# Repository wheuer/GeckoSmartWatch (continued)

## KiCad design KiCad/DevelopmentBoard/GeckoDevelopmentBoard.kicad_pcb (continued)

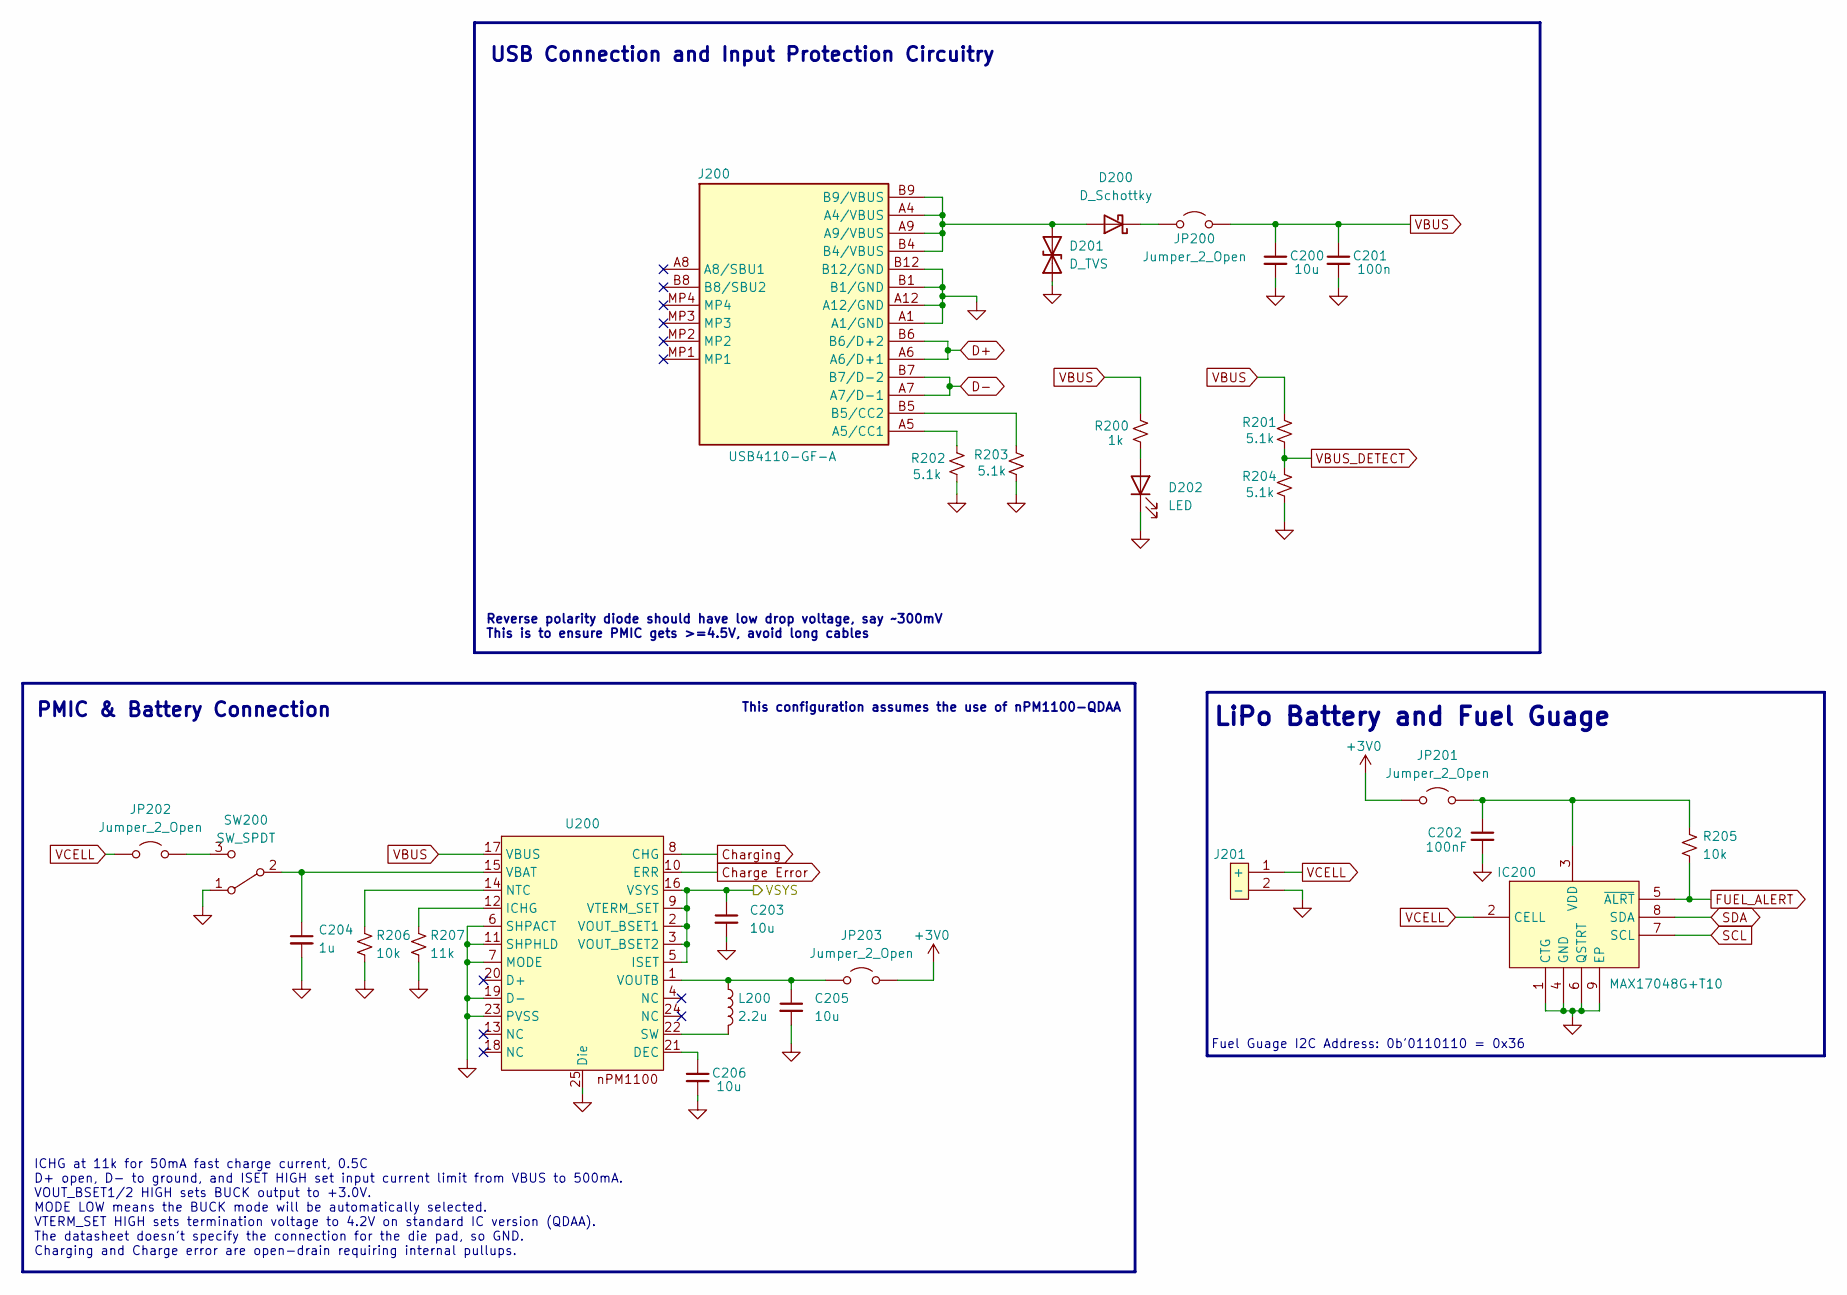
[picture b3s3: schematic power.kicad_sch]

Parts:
C200, C203, C205, C206: 10u; C_0402_1005Metric
C201: 100n; C_0402_1005Metric
C202: 100nF; C_0402_1005Metric
C204: 1u; C_0402_1005Metric
D200: D_Schottky; reversePolarity_SODFL3616X98N
D201: D_TVS; TVS_SOD2513X120N
D202: LED; LED_0603_1608Metric
IC200: MAX17048G+T10; MAX17048_fuelGuague; Mouser Part Number 700-MAX17048G+T10
J200: USB4110-GF-A; USB4110GFA; Mouser Part Number 640-USB4110-GF-A
J201: 1769_LiPoConnector; 1769_lipoConnector; Mouser Part Number 485-1769
JP200, JP201, JP202, JP203: Jumper_2_Open; 2pinJumper_HDRV2W110P0X254_1X2_508X254X854P
L200: 2.2u; L_0402_1005Metric
R200: 1k; R_0402_1005Metric
R201, R202, R203, R204: 5.1k; R_0402_1005Metric
R205, R206: 10k; R_0402_1005Metric
R207: 11k; R_0402_1005Metric
SW200: SW_SPDT; largerSlide_SW_JS102011JAQN
U200: nPM1100_QFN50P400X400X90-25N-D

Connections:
+3V0: JP201.1 (A), JP203.1 (A); also elsewhere on the board
/Power/VSYS: C203.1, U200.2 (VOUT_BSET1), U200.3 (VOUT_BSET2), U200.5 (ISET), U200.9 (VTERM_SET), U200.16 (VSYS)
Charge Error: U200.10 (ERR); also elsewhere on the board
Charging: U200.8 (CHG); also elsewhere on the board
D+: J200.A6 (A6/D+1), J200.B6 (B6/D+2); also elsewhere on the board
D-: J200.A7 (A7/D-1), J200.B7 (B7/D-2); also elsewhere on the board
FUEL_ALERT: IC200.5 (~ALRT), R205.1; also elsewhere on the board
GND: C200.2, C201.2, C202.2, C203.2, C204.2, C205.2, C206.2, D201.1 (A1), D202.1 (K), IC200.1 (CTG), IC200.4 (GND), IC200.6 (QSTRT), IC200.9 (EP), J200.A1 (A1/GND), J200.A12 (A12/GND), J200.B1 (B1/GND), J200.B12 (B12/GND), J201.2 (-), R202.1, R203.1, R204.1, R206.2, R207.2, SW200.1 (A), U200.6 (SHPACT), U200.7 (MODE), U200.11 (SHPHLD), U200.19 (D-), U200.23 (PVSS), U200.25 (Die); also elsewhere on the board
unnamed: D200.2 (A), D201.2 (A2), J200.A4 (A4/VBUS), J200.A9 (A9/VBUS), J200.B4 (B4/VBUS), J200.B9 (B9/VBUS)
unnamed: D200.1 (K), JP200.2 (B)
unnamed: D202.2 (A), R200.2
unnamed: C202.1, IC200.3 (VDD), JP201.2 (B), R205.2
unnamed: J200.A5 (A5/CC1), R202.2
unnamed: J200.B5 (B5/CC2), R203.2
unnamed: JP202.2 (B), SW200.3 (C)
unnamed: C205.1, JP203.2 (B), L200.1, U200.1 (VOUTB)
unnamed: C204.1, SW200.2 (B), U200.15 (VBAT)
unnamed: C206.1, U200.21 (DEC)
unnamed: R207.1, U200.12 (ICHG)
unnamed: R206.1, U200.14 (NTC)
unnamed: L200.2, U200.22 (SW)
SCL: IC200.7 (SCL); also elsewhere on the board
SDA: IC200.8 (SDA); also elsewhere on the board
VBUS: C200.1, C201.1, JP200.1 (A), R200.1, R201.2, U200.17 (VBUS); also elsewhere on the board
VBUS_DETECT: R201.1, R204.2; also elsewhere on the board
VCELL: IC200.2 (CELL), J201.1 (+), JP202.1 (A)

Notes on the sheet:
This configuration assumes the use of nPM1100-QDAA
USB Connection and Input Protection Circuitry
ICHG at 11k for 50mA fast charge current, 0.5C D+ open, D- to ground, and ISET HIGH set input current limit from VBUS to 500mA. VOUT_BSET1/2 HIGH sets BUCK output to +3.0V. MODE LOW means the BUCK mode will be automatically selected. VTERM_SET HIGH sets termination voltage to 4.2V on standard IC ve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
Fuel Guage I2C Address: 0b'0110110 = 0x36
PMIC & Battery Connection
Reverse polarity diode should have low drop voltage, say ~300mV This is to ensure PMIC gets >=4.5V, avoid long cables
LiPo Battery and Fuel Guage

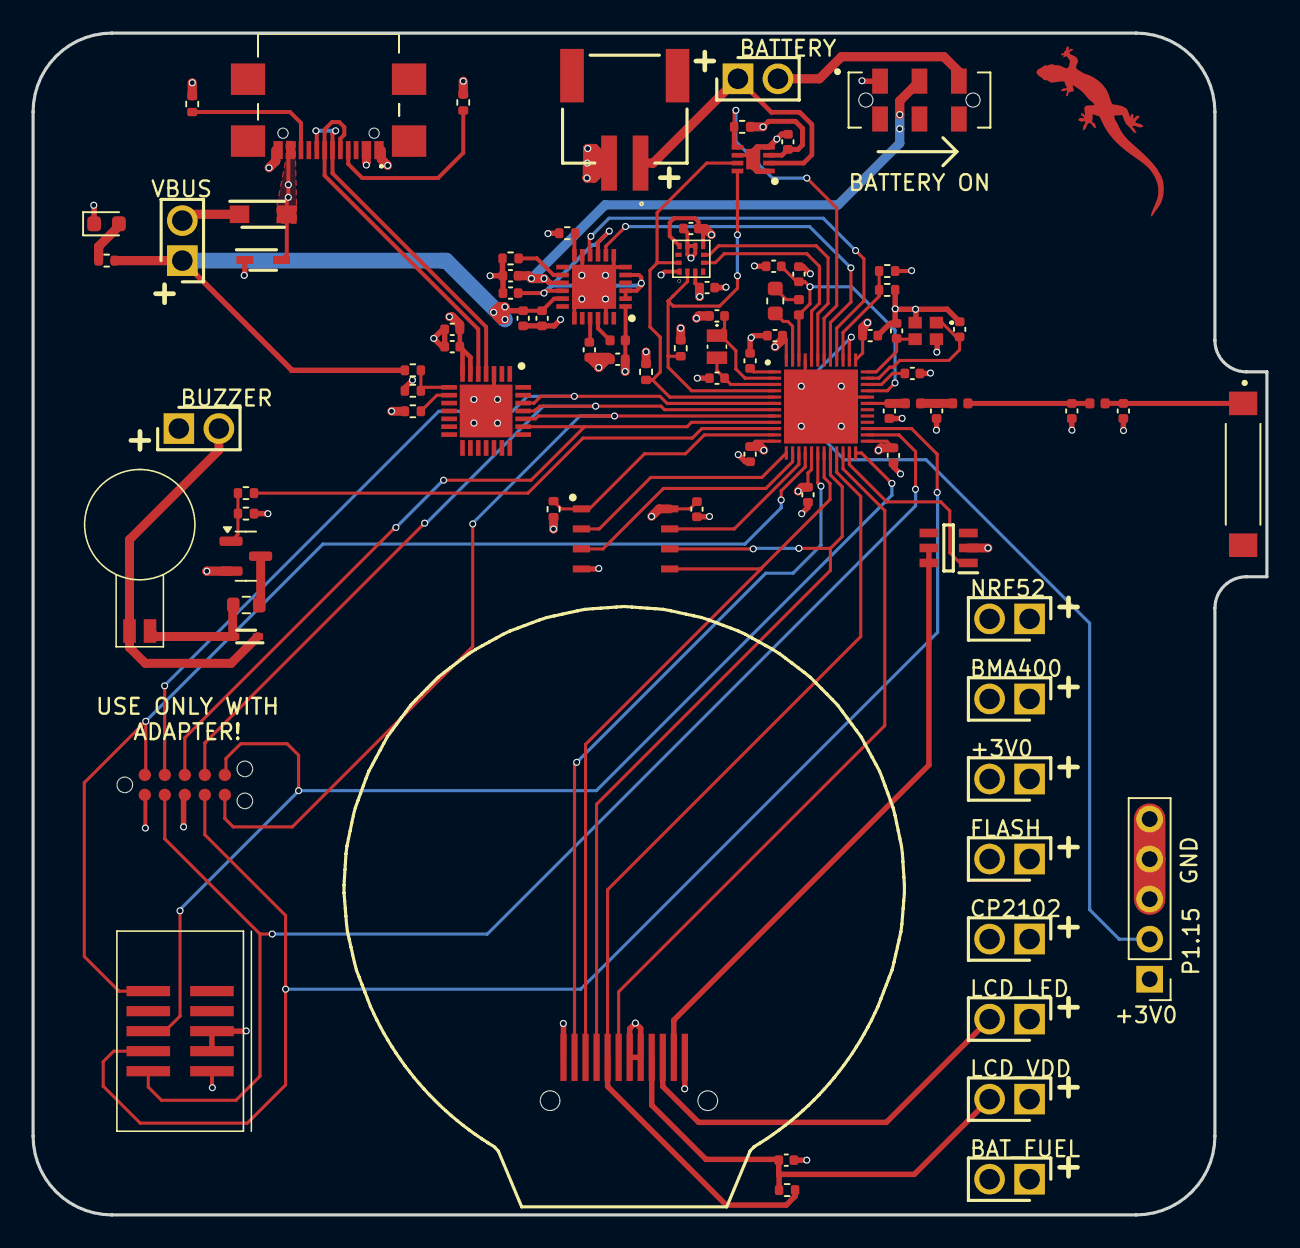
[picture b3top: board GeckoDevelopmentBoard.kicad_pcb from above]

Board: 4 copper layers, 78.3 x 75.0 mm, 88 parts (0 on the bottom side), 74 nets.

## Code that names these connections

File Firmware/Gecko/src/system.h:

#ifndef __MAIN__H
#define __MAIN__H

#include <zephyr/kernel.h>
#include <zephyr/drivers/gpio.h>
#include <nrfx.h>
#include <time.h>
#include <stdio.h>
#include "console.h"

#define __DEVELOPMENT_BOARD__ 1

/* 
    Thread priorites:
    Lower value is higher priority
    Negative priorities will never be preempted 
    Main thread has a default priority of 0
*/
#define TAPS_THREAD_PRIORITY 5

/* System Events */
#define SYSTEM_EVENT_DOUBLE_TAP         0x01
#define SYSTEM_EVENT_SINGLE_TAP         0x02
#define SYSTEM_EVENT_TIMEOUT            0x04
#define SYSTEM_EVENT_TIME_UPDATE        0x08
#define SYSTEM_EVENT_NEW_NOTIFICATION   0x10
#define SYSTEM_EVENT_MAIN_MASK          0x1F // 0b'11111

/* Generic Device Labels */
#define PWM_DEVICE_LABEL        DT_NODELABEL(pwm0)
#define GPIO_0_DEVICE_LABEL     DT_NODELABEL(gpio0)
#define GPIO_1_DEVICE_LABEL     DT_NODELABEL(gpio1)
#define SPI_DEVICE_LABEL        DT_NODELABEL(spi3)
#define UART_DEVICE_LABEL       DT_NODELABEL(uart0)
#define I2C_DEVICE_LABEL        DT_NODELABEL(i2c0)
#if !__DEVELOPMENT_BOARD__
    #define ADC_DEVICE_LABEL        DT_NODELABEL(adc)
#endif

/* SPI Pins */
#if __DEVELOPMENT_BOARD__
    #define SCK_PIN 21
    #define MOSI_PIN 20
    #define MISO_PIN 13
#else
    #define SCK_PIN 19
    #define MOSI_PIN 14
    #define MISO_PIN 13
#endif

/* I2C Device Address' */
#define FUEL_GUAGE_I2C_ADDRESS  0x36
#define BMA400_I2C_ADDRESS      0x14

/* BLE Defines */
#define BT_DEVICE_NAME      CONFIG_BT_DEVICE_NAME
#define BT_DEVICE_NAME_LEN  (sizeof(BT_DEVICE_NAME) - 1)

/* LCD Pins and Port */
#define DISPLAY_START_BRIGHTNESS    60 // %
#define BRIGHTNESS_STEP             20 // %

#if __DEVELOPMENT_BOARD__
    #define LCD_RESET_PIN           19 // P0.19
    #define LCD_CS_PIN              22 // P0.22
    #define LCD_DC_PIN              23 // P0.23
    #define LCD_PWM_CHANNEL         0  // PWM_OUT0 -> Pin is defined in the devicetree
    #define LCD_PWM_PERIOD          PWM_USEC(50) // 10 kHz    
#else
    #define LCD_RESET_PIN           17 // P0.17
    #define LCD_CS_PIN              20 // P0.20
    #define LCD_DC_PIN              21 // P0.21
    #define LCD_PWM_CHANNEL         0  // P0.22, PWM_OUT0
    #define LCD_PWM_PERIOD          PWM_USEC(50) // 10 kHz    
#endif

/* Accelerometer (BMA400) Pins*/
#if __DEVELOPMENT_BOARD__
    #define BMA_INT1_PIN    31 // P0.31
    #define BMA_INT2_PIN    30 // P0.30
#else
    #define BMA_CS_PIN      8  // P1.08
    #define BMA_INT1_PIN    11 // P0.11
    #define BMA_INT2_PIN    9  // P1.09
#endif

/* External FLASH Pins */
#if __DEVELOPMENT_BOARD__
    #define EFLASH_CS_PIN   12  // P0.12
    #define EFLASH_WP_PIN   14  // P0.14
    #define EFLASH_HOLD_PIN 17  // P0.17
#else
    #define EFLASH_CS_PIN   8  // P0.08
    #define EFLASH_WP_PIN   7  // P0.07
    #define EFLASH_HOLD_PIN 12 // P0.12
#endif

/* Buzzer Pins */
// The buzzer pin is defined in the device tree
#define BUZZER_PWM_PERIOD       PWM_USEC(50) // 10 kHz
#define BUZZER_PWM_CHANNEL      1            // PWM_OUT1 -> Pin is defined in the devicetree


/* Power Management (nPM1100) and ADC Pins */
#define PWR_ADC_RESOLUTION          12
#define PWR_ADC_CHANNEL             0
#define PWR_ADC_PORT                SAADC_CH_PSELP_PSELP_AnalogInput6 // P0.30, AIN6
#define PWR_ADC_GAIN                ADC_GAIN_1_6 // 1/6 gain, this is the reset value
#define PWR_ADC_REFERENCE           ADC_REF_INTERNAL // 0.6 V, which is default
#define PWR_ADC_ACQUISITION_TIME    ADC_ACQ_TIME(ADC_ACQ_TIME_MICROSECONDS, 40) // 40 is the highest

#if __DEVELOPMENT_BOARD__
    #define PWR_CHARGE_ERR_PIN  2  // P0.02
    #define PWR_CHARGING_PIN    28 // P0.28
#else
    #define PWR_CHARGE_ERR_PIN  4 // P0.04
    #define PWR_CHARGING_PIN    5 // P0.05
#endif

extern struct spi_config spi_cfg;

extern time_t currentSystemTime;
extern bool screenState;
extern volatile bool bluetoothConnected;

extern const struct device* uart0_dev;
extern const struct device* pwm_dev;
extern const struct device* gpio0_dev;
extern const struct device* gpio1_dev;
extern const struct device* spi_dev;
extern const struct device* adc_dev;
extern const struct device* i2c_dev;

extern struct k_event userInteractionEvent;

extern volatile bool spiEnabled;

void disableSPI(void);
void enableSPI(void);

#endif // __MAIN_H

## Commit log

2024-07-24 [Repo Setup] Initial commit of current development progress
2024-08-08 [Base Firmware/PCB] Implement bare system functionality and add V4 schematic and PCB
2024-09-02 [Accelerometer/Taps] Test other BMA400 tap events
2025-03-07 [Firmware/Android App] Major updates from local development
2025-03-27 [Fuel Guage/README] Add some fuel guage implementation code for future use and update README.
2025-06-30 [Android App] Make phone-watch connection more robust and add specific package filtering for notifications
